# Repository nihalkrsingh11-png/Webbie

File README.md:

# Webbie V1.0
**Your Personal Spider Companion**
---
This is a project developed by me (Nihal) for the Week 1 (PCB design) of HackClub's Halflife Event🔥
---
A custom motion controlled digital bot which is shaped like a spider (hence the name Webbie). It has been designed sit on your desk (can also be used as a locket) and showcase its personality on a display. It has been equipped with a microcontroller, buzzer, motion sensor, display and environmental sensor, all fitted in a compact spider pcb design.

## PROJECT SHOWCASE

**Hardware Specs**
---
**Microcontroller**: ESP 32 C3 SMD

**Sensors**: DHT11 and MPU6050

**Audio**: Buzzer

**Display**: 0.96" OLED

**Wiring Diagram or Schematic**
---

**Copper Tracing and Silk Screen Preview**
---

**3D File Design**
---
**Assembled (with PCB)**
---

**Assembled (without PCB)**
---

**3D Print Ready**
---

## Designed the 3D files in Autodesk Fusion

**Code:**
---
The code has been uploaded in Firmware/Webbie.ino

## Thanks for reading.

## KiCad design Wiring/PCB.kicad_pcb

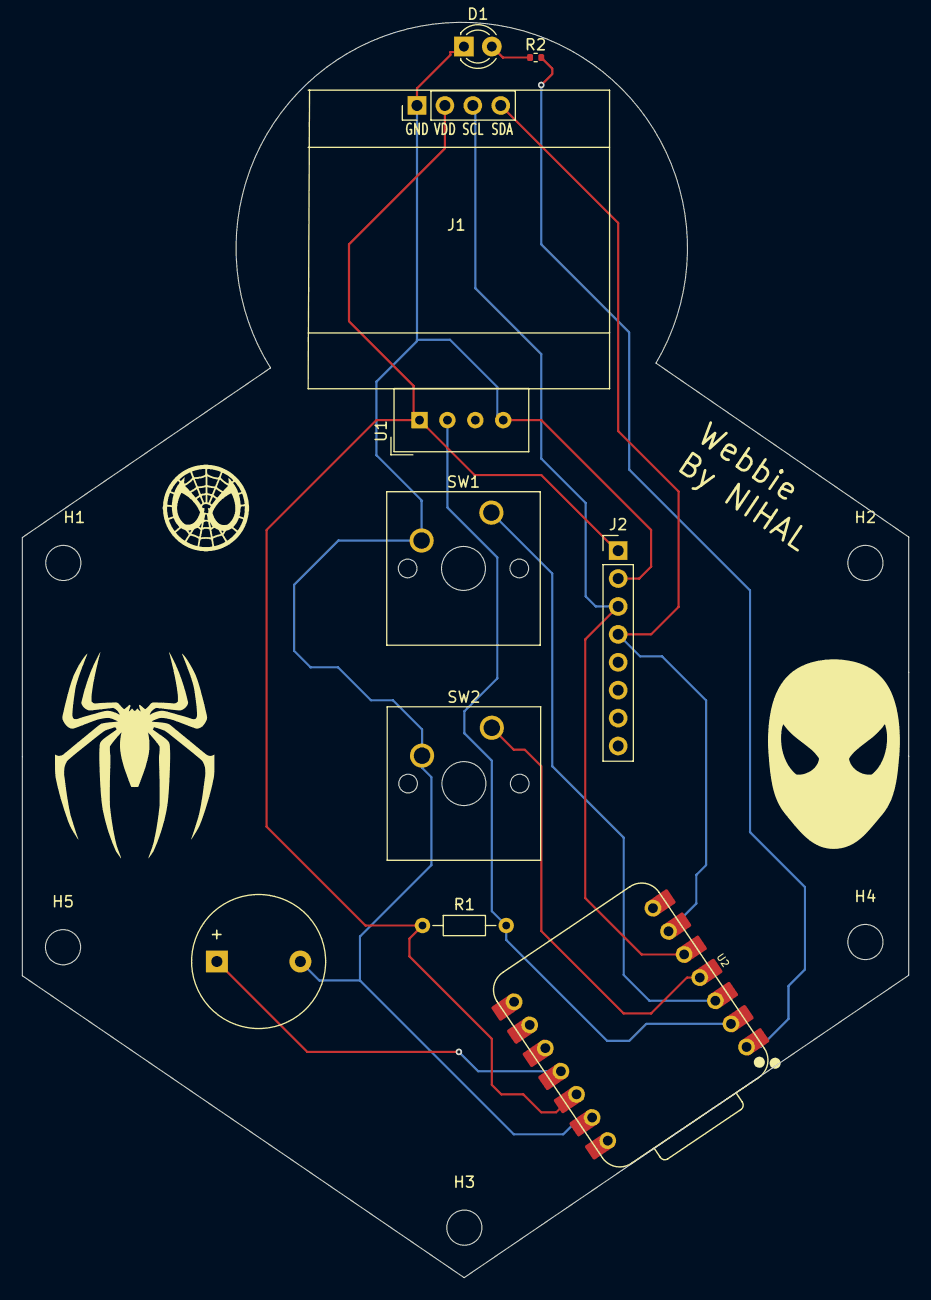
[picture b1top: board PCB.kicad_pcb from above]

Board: 2 copper layers, 80.7 x 114.3 mm, 15 parts (0 on the bottom side), 10 nets.

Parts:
BZ1: Buzzer; Buzzer_12x9.5RM7.6
D1: LED; LED_D3.0mm
H1, H2, H3, H4, H5: MountingHole; MountingHole_3.2mm_M3
J1: Conn_01x04_Pin; Display_128x64_096_I2C
J2: Conn_01x08_Pin; PinHeader_1x08_P2.54mm_Vertical
R1: 10k; R_Axial_DIN0204_L3.6mm_D1.6mm_P7.62mm_Horizontal
R2: 220; R_0402_1005Metric
SW1, SW2: SW_Push; SW_Cherry_MX_1.00u_PCB
U1: DHT11; Aosong_DHT11_5.5x12.0_P2.54mm
U2: XIAO-ESP32-C3-SMD; XIAO-ESP32-C6-DIP

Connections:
+3.3V: J1.2, J2.1, R1.1, U1.1 (VDD), U2.12 (3V3_OUT)
/<NO NET>: R1.2, U1.2 (DATA), U2.2 (D1)
/BUZZ: BZ1.1 (+), U2.11 (D10)
/GPIO2: SW1.1, U2.3 (D2)
/GPIO3: SW2.1, U2.4 (D3)
/LEDP: R2.2, U2.1 (D0)
/SCL: J1.3, J2.3, U2.5 (D4)
/SDA: J1.4, J2.4, U2.6 (D5)
GND: BZ1.2 (-), D1.1 (K), J1.1, J2.2, SW1.2, SW2.2, U1.4 (GND), U2.13 (GND)
unnamed: D1.2 (A), R2.1
